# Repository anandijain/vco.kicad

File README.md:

# kicad 

following all of the diy boards by moritz klein

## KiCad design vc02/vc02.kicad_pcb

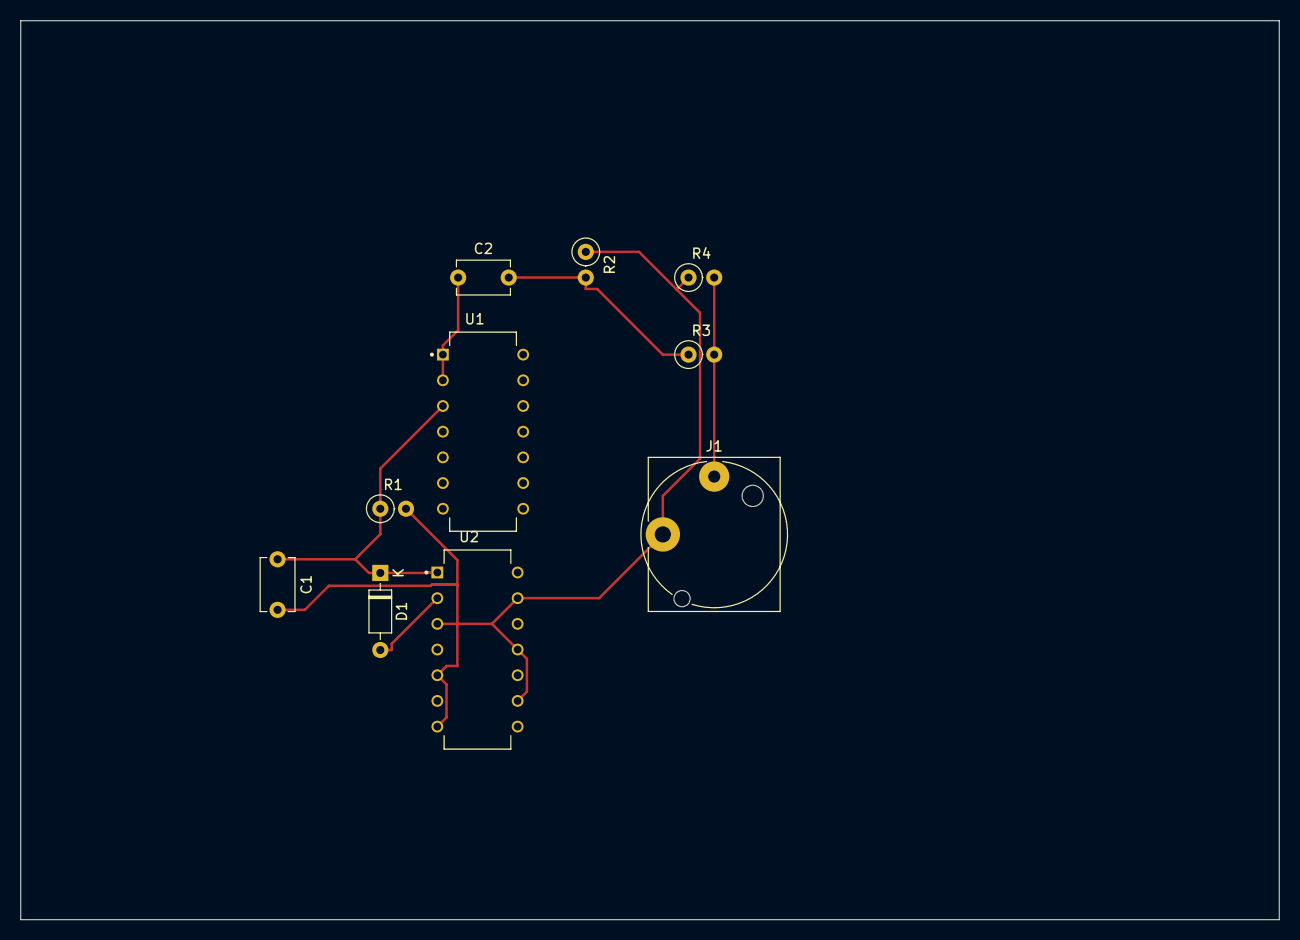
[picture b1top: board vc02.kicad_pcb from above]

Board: 2 copper layers, 124.5 x 88.9 mm, 10 parts (0 on the bottom side), 6 nets.

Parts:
C1, C2: C; C_Disc_D5.1mm_W3.2mm_P5.00mm
D1: 1N4148; D_DO-35_SOD27_P7.62mm_Horizontal
J1: AudioJack2; Jack_6.35mm_Neutrik_NJ2FD-V_Vertical
R1, R2, R3, R4: R; R_Axial_DIN0207_L6.3mm_D2.5mm_P2.54mm_Vertical
U1: TL074; DIP794W45P254L1969H508Q14
U2: 40106; DIP794W45P254L1969H508Q14

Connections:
GND: C1.2, J1.S, R1.2, R2.1, R4.1, U2.3, U2.5, U2.7 (VSS), U2.9, U2.11, U2.13
unnamed: C2.2, R2.2, R3.1
unnamed: D1.2 (A), U2.2
unnamed: C1.1, D1.1 (K), R1.1, U1.3 (+), U2.1
unnamed: J1.T, R3.2, R4.2
unnamed: C2.1, U1.1, U1.2 (-)

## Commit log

2023-11-03 init
2023-11-03 episode 1 schematic finished, also git ignore
2023-11-03 pot on npn
2023-11-07 traces
